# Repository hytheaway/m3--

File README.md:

# m3-- (or aoifernet)

more info can be found at https://hytheaway.github.io/projects/aoifernet.html

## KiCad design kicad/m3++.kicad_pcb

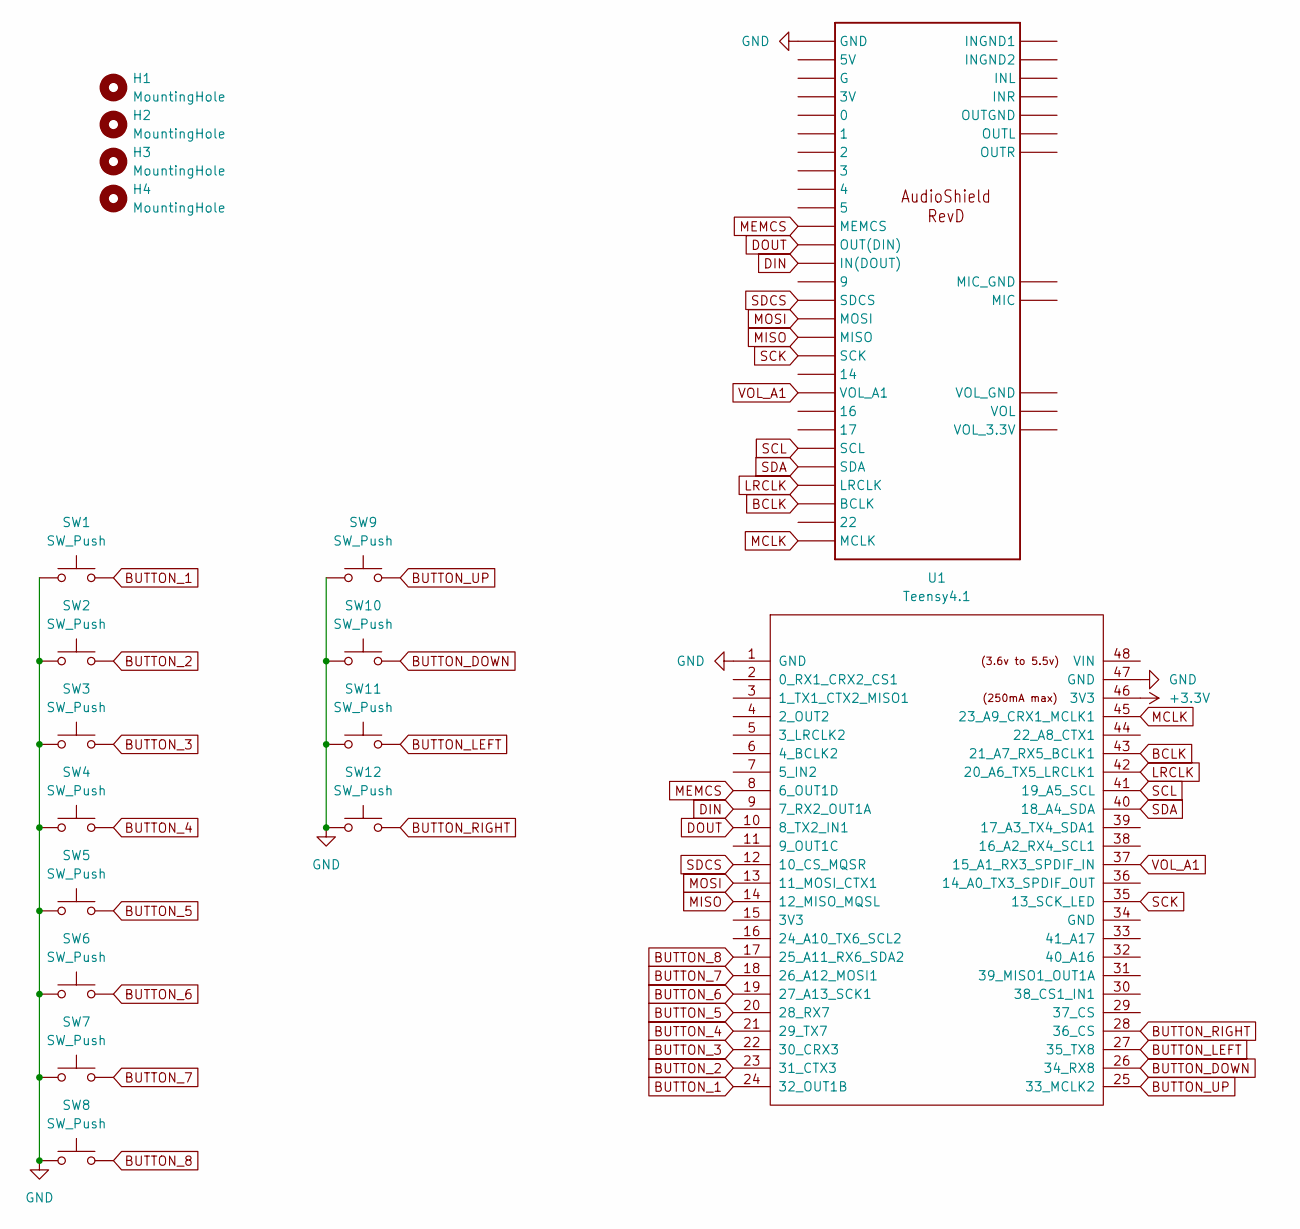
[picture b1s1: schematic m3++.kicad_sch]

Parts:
1: 4.0audioshield
H1, H2, H3, H4: MountingHole; MountingHole_2.7mm
SW1, SW2, SW3, SW4, SW5, SW6, SW7, SW8, SW9, SW10, SW11, SW12: SW_Push; SW_Cherry_MX_1.00u_PCB
U1: Teensy4.1; Teensy41

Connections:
+3.3V: U1.46 (3V3)
BCLK: 1.21 (BCLK), U1.43 (21_A7_RX5_BCLK1)
BUTTON_1: SW1.2, U1.24 (32_OUT1B)
BUTTON_2: SW2.2, U1.23 (31_CTX3)
BUTTON_3: SW3.2, U1.22 (30_CRX3)
BUTTON_4: SW4.2, U1.21 (29_TX7)
BUTTON_5: SW5.2, U1.20 (28_RX7)
BUTTON_6: SW6.2, U1.19 (27_A13_SCK1)
BUTTON_7: SW7.2, U1.18 (26_A12_MOSI1)
BUTTON_8: SW8.2, U1.17 (25_A11_RX6_SDA2)
BUTTON_DOWN: SW10.2, U1.26 (34_RX8)
BUTTON_LEFT: SW11.2, U1.27 (35_TX8)
BUTTON_RIGHT: SW12.2, U1.28 (36_CS)
BUTTON_UP: SW9.2, U1.25 (33_MCLK2)
DIN: 1.8 (IN(DOUT)), U1.9 (7_RX2_OUT1A)
DOUT: 1.7 (OUT(DIN)), U1.10 (8_TX2_IN1)
GND: 1.GND, SW1.1, SW2.1, SW3.1, SW4.1, SW5.1, SW6.1, SW7.1, SW8.1, SW9.1, SW10.1, SW11.1, SW12.1, U1.1 (GND), U1.47 (GND)
LRCLK: 1.20 (LRCLK), U1.42 (20_A6_TX5_LRCLK1)
MCLK: 1.23 (MCLK), U1.45 (23_A9_CRX1_MCLK1)
MEMCS: 1.6 (MEMCS), U1.8 (6_OUT1D)
MISO: 1.12 (MISO), U1.14 (12_MISO_MQSL)
MOSI: 1.11 (MOSI), U1.13 (11_MOSI_CTX1)
SCK: 1.13 (SCK), U1.35 (13_SCK_LED)
SCL: 1.19 (SCL), U1.41 (19_A5_SCL)
SDA: 1.18 (SDA), U1.40 (18_A4_SDA)
SDCS: 1.10 (SDCS), U1.12 (10_CS_MQSR)
VOL_A1: 1.15 (VOL_A1), U1.37 (15_A1_RX3_SPDIF_IN)

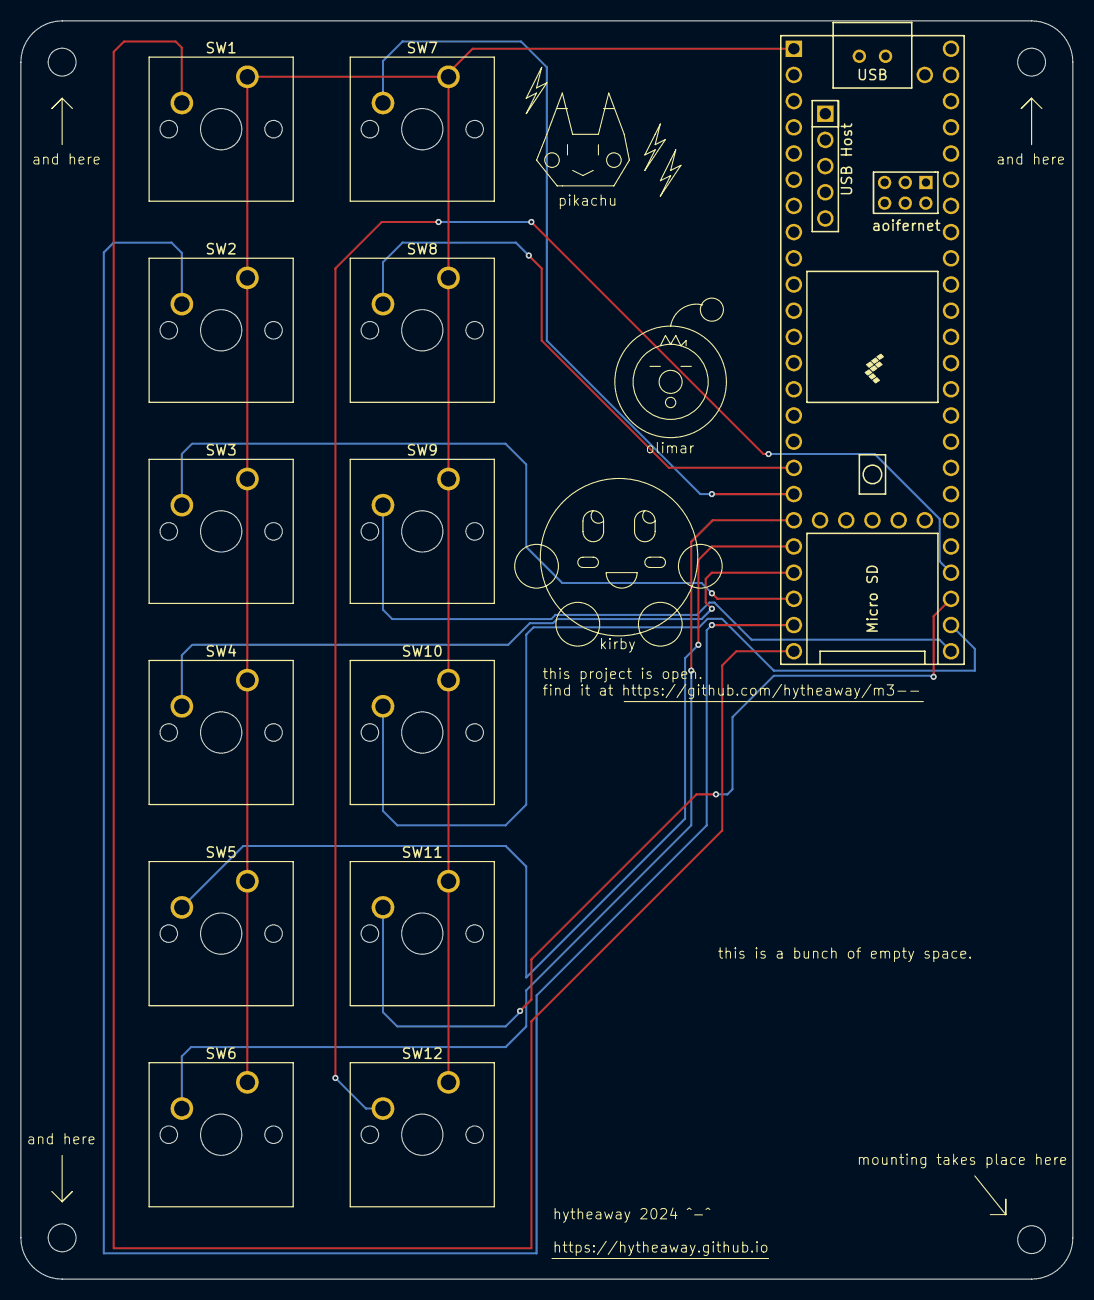
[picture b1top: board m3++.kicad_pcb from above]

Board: 2 copper layers, 102.0 x 122.0 mm, 17 parts (0 on the bottom side), 13 nets.

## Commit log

2024-11-16 finished pcb design
    design files when ordered
2024-12-19 updated files
